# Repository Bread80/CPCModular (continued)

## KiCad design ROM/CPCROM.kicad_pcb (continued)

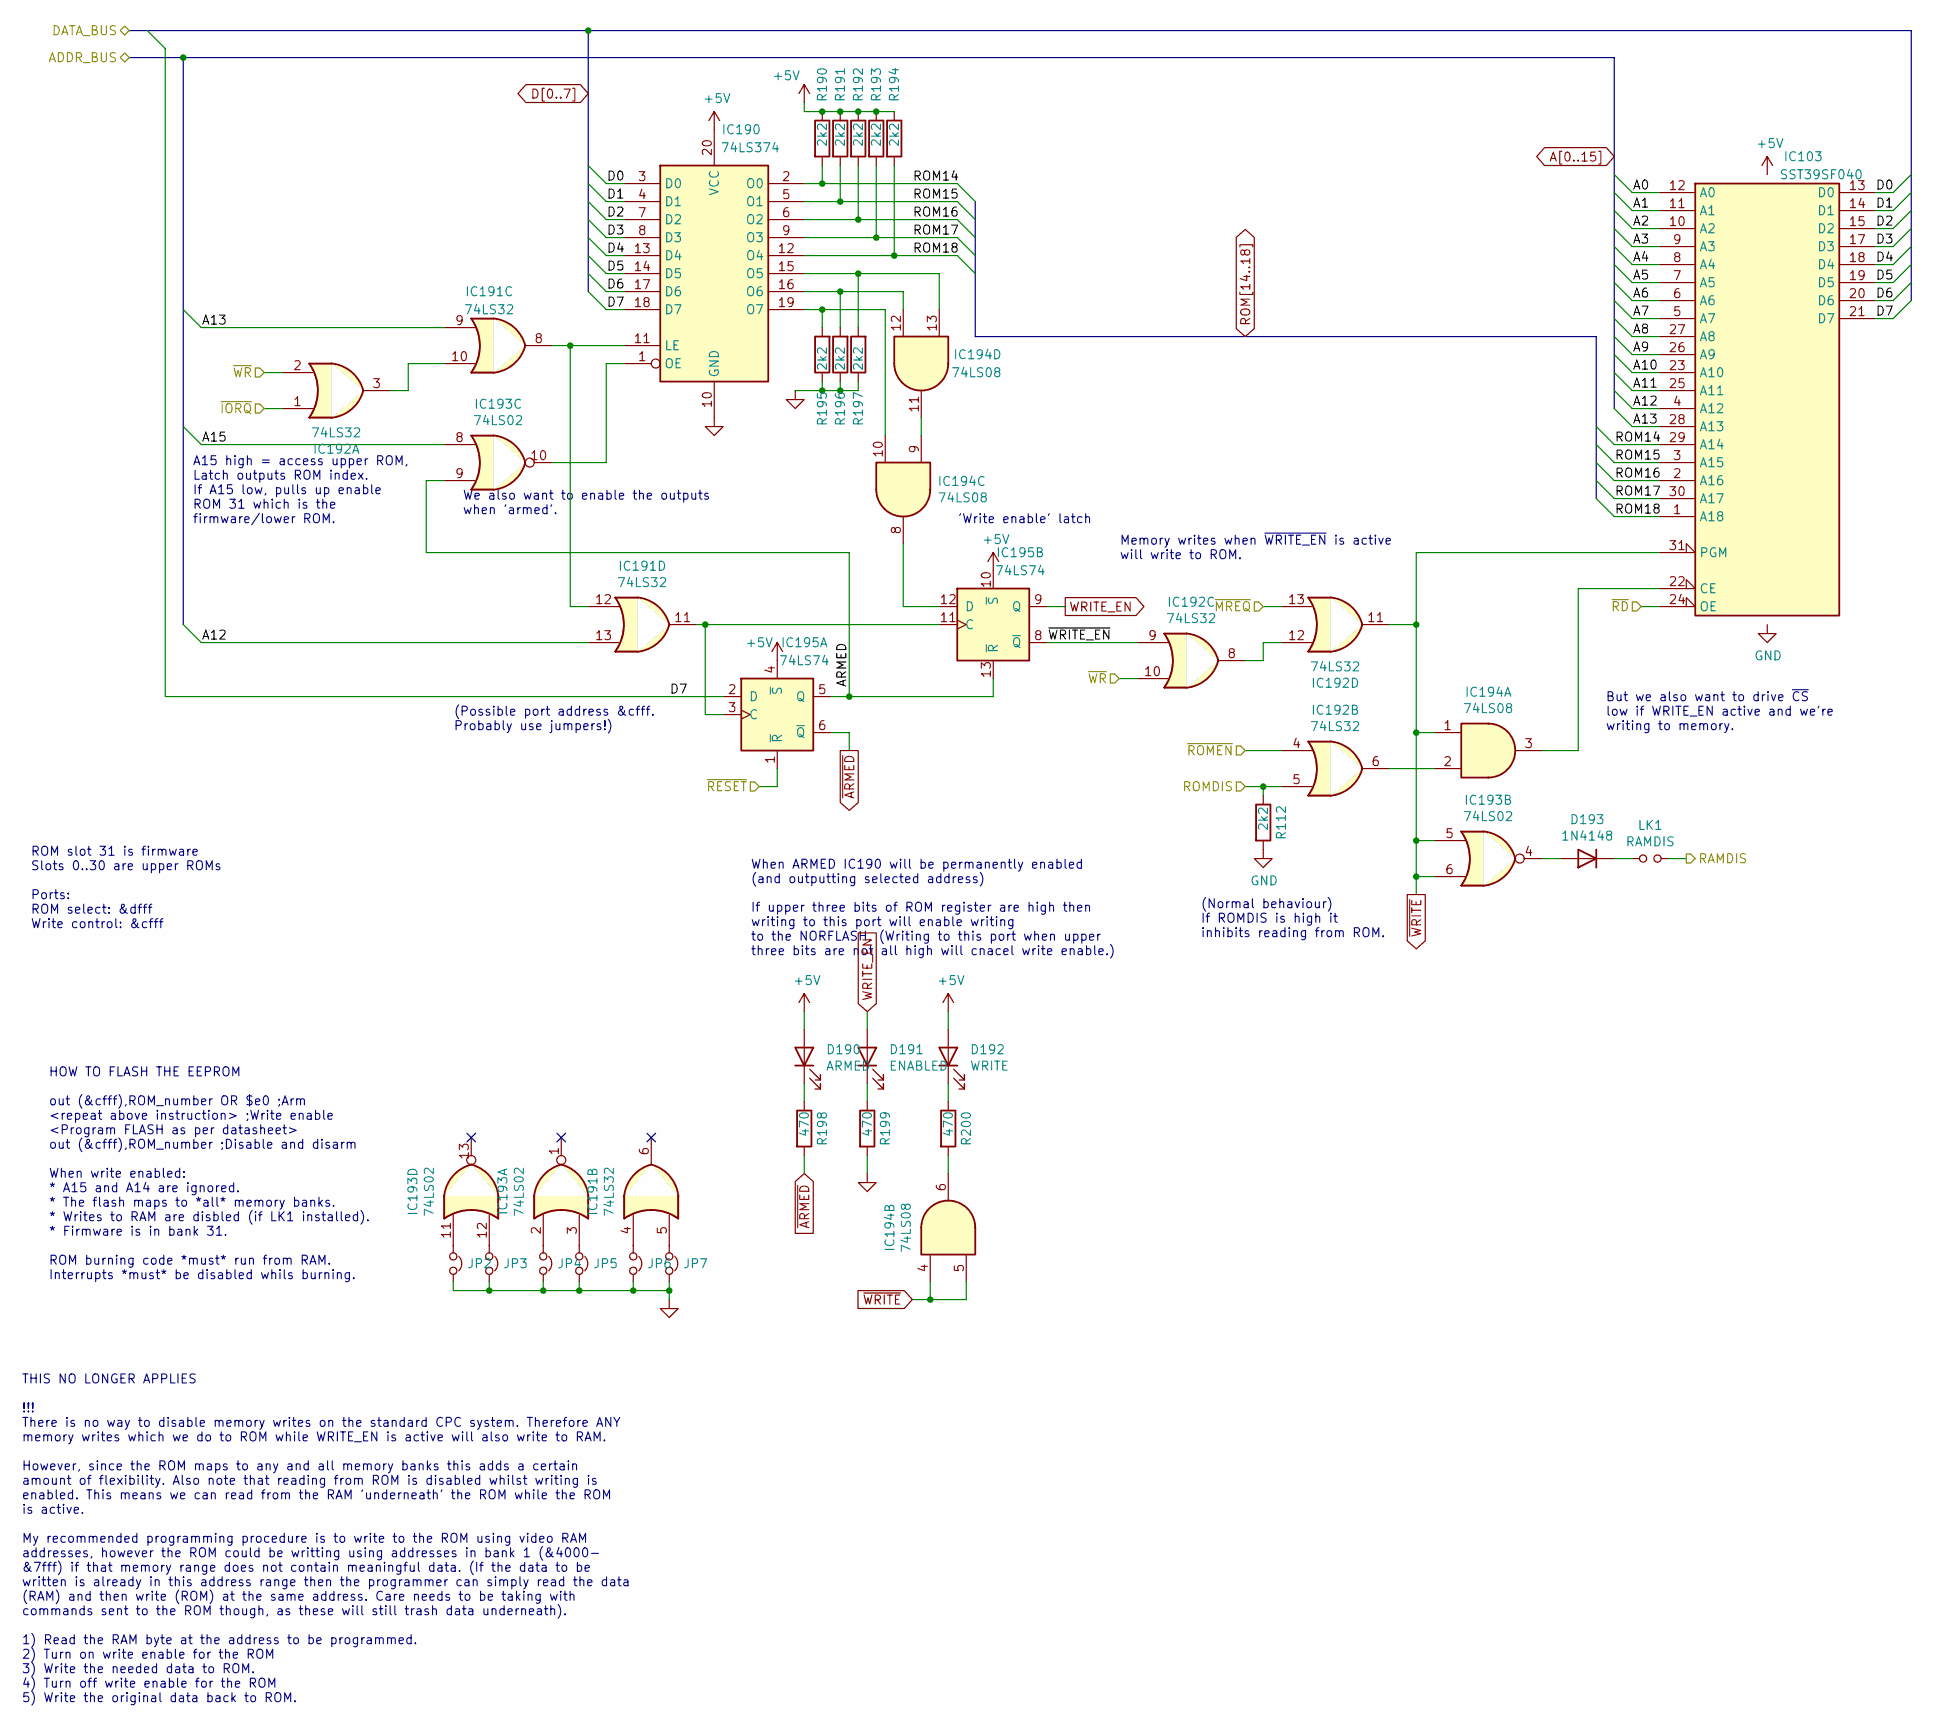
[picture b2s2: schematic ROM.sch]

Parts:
D190: ARMED; LED_D3.0mm
D191: ENABLED; LED_D3.0mm
D192: WRITE; LED_D3.0mm
D193: 1N4148; D_DO-35_SOD27_P7.62mm_Horizontal
IC103: SST39SF040; DIP_Socket-32_W11.9_W12.7_W15.24_W17.78_W18.5_3M_232-1285-0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
IC190: 74LS374; DIP-20_W7.62mm_Socket
IC191, IC192: 74LS32; DIP-14_W7.62mm_Socket
IC193: 74LS02; DIP-14_W7.62mm_Socket
IC194: 74LS08; DIP-14_W7.62mm_Socket
IC195: 74LS74; DIP-14_W7.62mm_Socket
JP2, JP3, JP4, JP5, JP6, JP7: Jumper_NC_Small; SolderJumper-2_P1.3mm_Bridged_RoundedPad1.0x1.5mm
LK1: RAMDIS; PinHeader_1x02_P2.54mm_Vertical
R112, R190, R191, R192, R193, R194, R195, R196, R197: 2k2; R_Axial_DIN0207_L6.3mm_D2.5mm_P7.62mm_Horizontal
R198, R199, R200: 470; R_Axial_DIN0207_L6.3mm_D2.5mm_P7.62mm_Horizontal

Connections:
/RAMDIS: LK1.2; also elsewhere on the board
/ROM/~WRITE_EN: IC192.9, IC195.8 (~Q)
/ROMDIS: IC192.5, R112.1; also elsewhere on the board
/~IORQ: IC192.1; also elsewhere on the board
/~MREQ: IC192.13; also elsewhere on the board
/~RD: IC103.24 (OE); also elsewhere on the board
/~RESET: IC195.1 (~R); also elsewhere on the board
/~ROMEN: IC192.4; also elsewhere on the board
A0: IC103.12 (A0); also elsewhere on the board
A1: IC103.11 (A1); also elsewhere on the board
A2: IC103.10 (A2); also elsewhere on the board
A3: IC103.9 (A3); also elsewhere on the board
A4: IC103.8 (A4); also elsewhere on the board
A5: IC103.7 (A5); also elsewhere on the board
A6: IC103.6 (A6); also elsewhere on the board
A7: IC103.5 (A7); also elsewhere on the board
A8: IC103.27 (A8); also elsewhere on the board
A9: IC103.26 (A9); also elsewhere on the board
A10: IC103.23 (A10); also elsewhere on the board
A11: IC103.25 (A11); also elsewhere on the board
A12: IC103.4 (A12), IC191.13; also elsewhere on the board
A13: IC103.28 (A13), IC191.9; also elsewhere on the board
D0: IC103.13 (D0), IC190.3 (D0); also elsewhere on the board
D1: IC103.14 (D1), IC190.4 (D1); also elsewhere on the board
D2: IC103.15 (D2), IC190.7 (D2); also elsewhere on the board
D3: IC103.17 (D3), IC190.8 (D3); also elsewhere on the board
D4: IC103.18 (D4), IC190.13 (D4); also elsewhere on the board
D5: IC103.19 (D5), IC190.14 (D5); also elsewhere on the board
D6: IC103.20 (D6), IC190.17 (D6); also elsewhere on the board
D7: IC103.21 (D7), IC190.18 (D7), IC195.2 (D); also elsewhere on the board
unnamed: D190.1 (K), R198.1
unnamed: D191.1 (K), R199.1
unnamed: D192.1 (K), R200.1
unnamed: D193.1 (K), LK1.1
unnamed: D193.2 (A), IC193.4
unnamed: IC103.22 (CE), IC194.3
unnamed: IC190.1 (OE), IC193.10
unnamed: IC190.11 (LE), IC191.8, IC191.12
unnamed: IC190.15 (O5), IC194.13, R197.2
unnamed: IC190.16 (O6), IC194.12, R196.2
unnamed: IC190.19 (O7), IC194.10, R195.2
unnamed: IC191.4, JP6.1
unnamed: IC191.5, JP7.1
unnamed: IC191.10, IC192.3
unnamed: IC192.6, IC194.2
unnamed: IC192.8, IC192.12
unnamed: IC193.2, JP4.1
unnamed: IC193.3, JP5.1
unnamed: IC194.6, R200.2
unnamed: IC194.9, IC194.11
ROM14: IC103.29 (A14), IC190.2 (O0), R190.2
ROM15: IC103.3 (A15), IC190.5 (O1), R191.2
ROM16: IC103.2 (A16), IC190.6 (O2), R192.2
ROM17: IC103.30 (A17), IC190.9 (O3), R193.2
ROM18: IC103.1 (A18), IC190.12 (O4), R194.2
WRITE_EN: D191.2 (A), IC195.9 (Q)
~ARMED: IC195.6 (~Q), R198.2

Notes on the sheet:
A15 high = access upper ROM, Latch outputs ROM index. If A15 low, pulls up enable ROM 31 which is the firmware/lower ROM.
'Write enable' latch
(Possible port address &cfff. Probably use jumpers!)
If upper three bits of ROM register are high then writing to this port will enable writing to the NORFLASH. (Writing to this port when upper three bits are not all high will cnacel write enable.)
Memory writes when ~WRITE_EN~ is active will write to ROM.
(Normal behaviour) If ROMDIS is high it inhibits reading from ROM.
But we also want to drive ~CS~ low if WRITE_EN active and we're writing to memory.
THIS NO LONGER APPLIES !!! There is no way to disable memory writes on the standard CPC system. Therefore ANY memory writes which we do to ROM while WRITE_EN is active will also write to RAM. However, since the ROM maps to any and all memory banks this adds a certain amount of flexibility. Also not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
HOW TO FLASH THE EEPROM out (&cfff),ROM_number OR $e0 ;Arm <repeat above instruction> ;Write enable <Program FLASH as per datasheet> out (&cfff),ROM_number ;Disable and disarm When write enabled: * A15 and A14 are ignored. * The flash maps to *all* memory banks. * Writes to RAM are disbled (if LK1 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
We also want to enable the outputs when 'armed'.
When ARMED IC190 will be permanently enabled (and outputting selected address)
ROM slot 31 is firmware Slots 0..30 are upper ROMs Ports: ROM select: &dfff Write control: &cfff

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
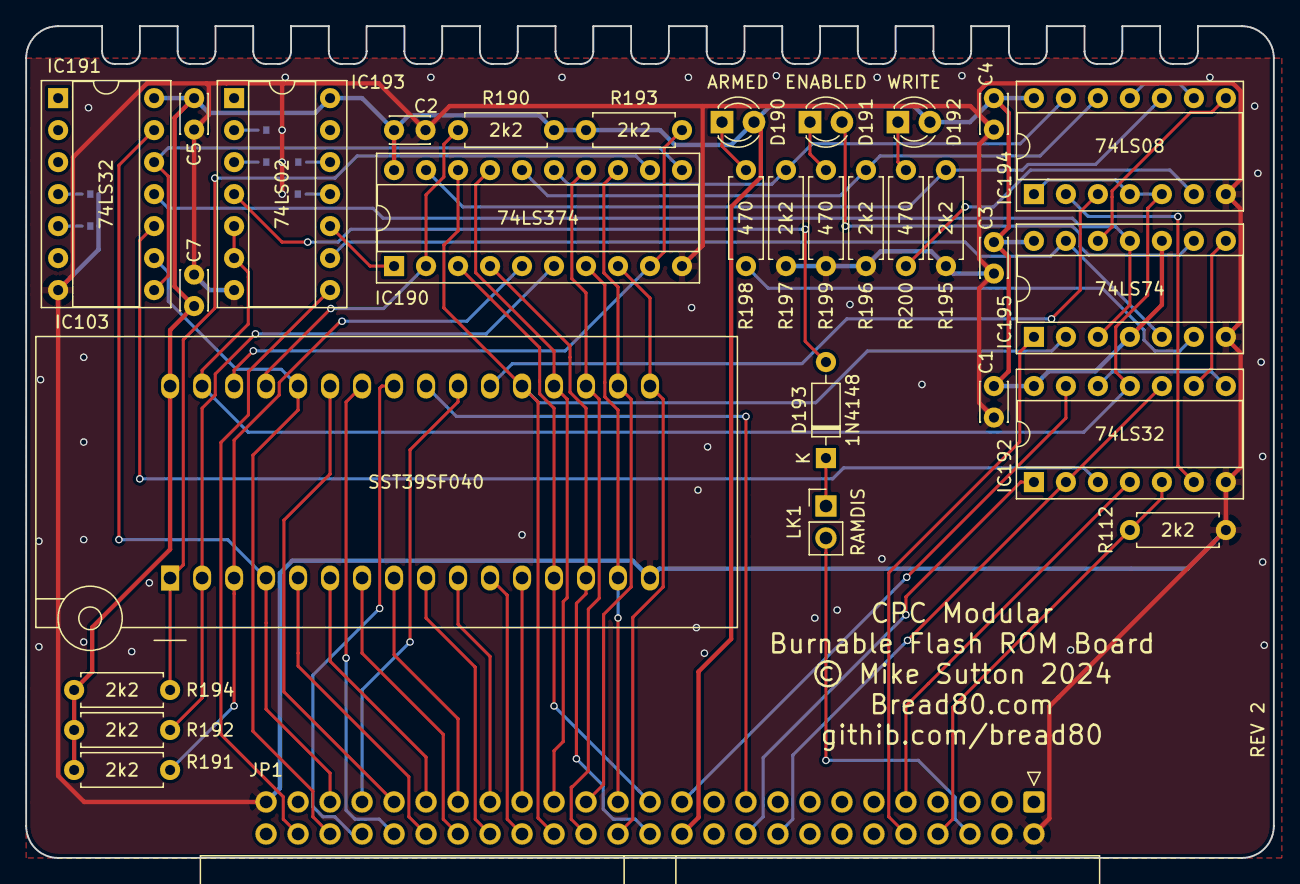
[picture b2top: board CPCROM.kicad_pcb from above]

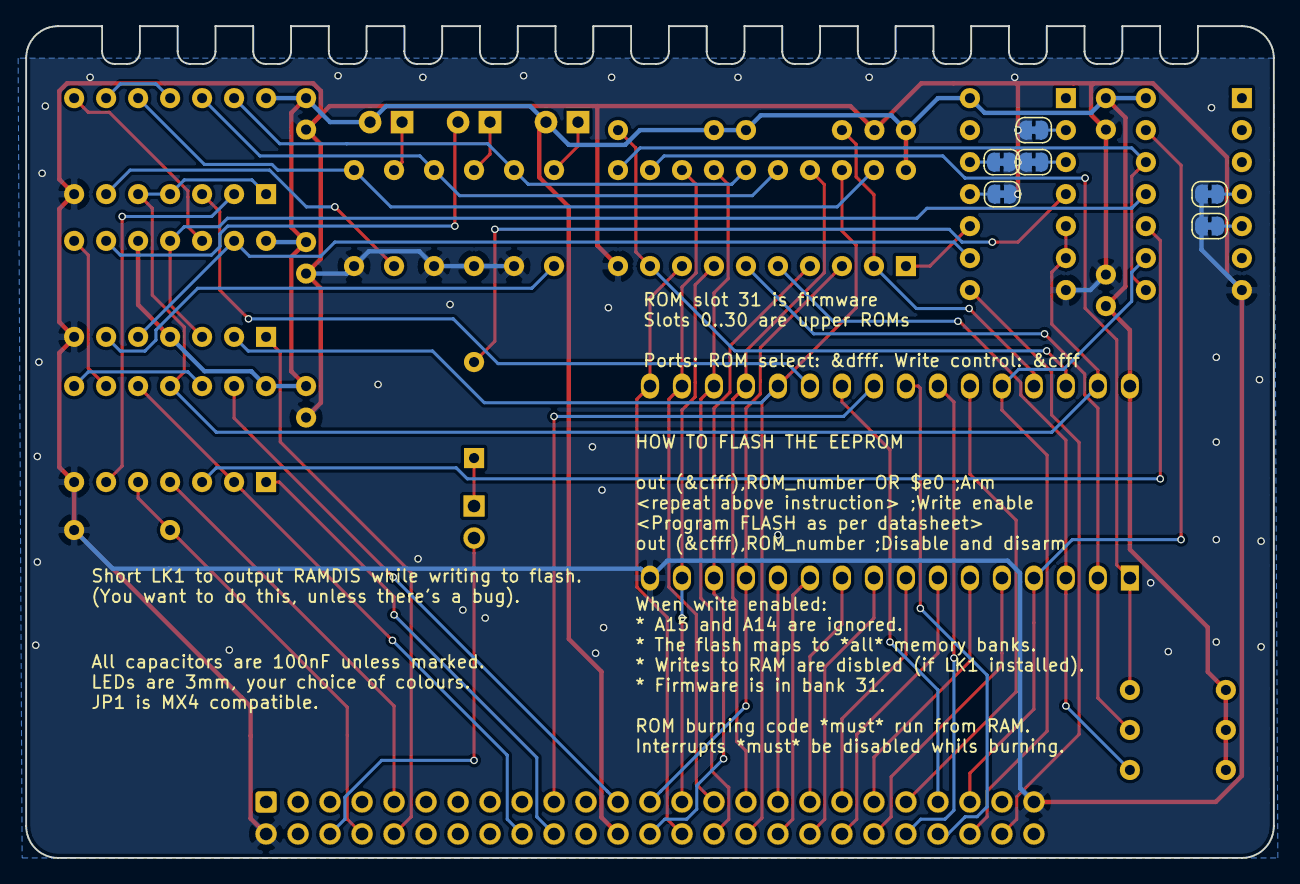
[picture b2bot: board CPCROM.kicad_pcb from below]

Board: 2 copper layers, 99.1 x 66.0 mm, 37 parts (6 on the bottom side), 67 nets.

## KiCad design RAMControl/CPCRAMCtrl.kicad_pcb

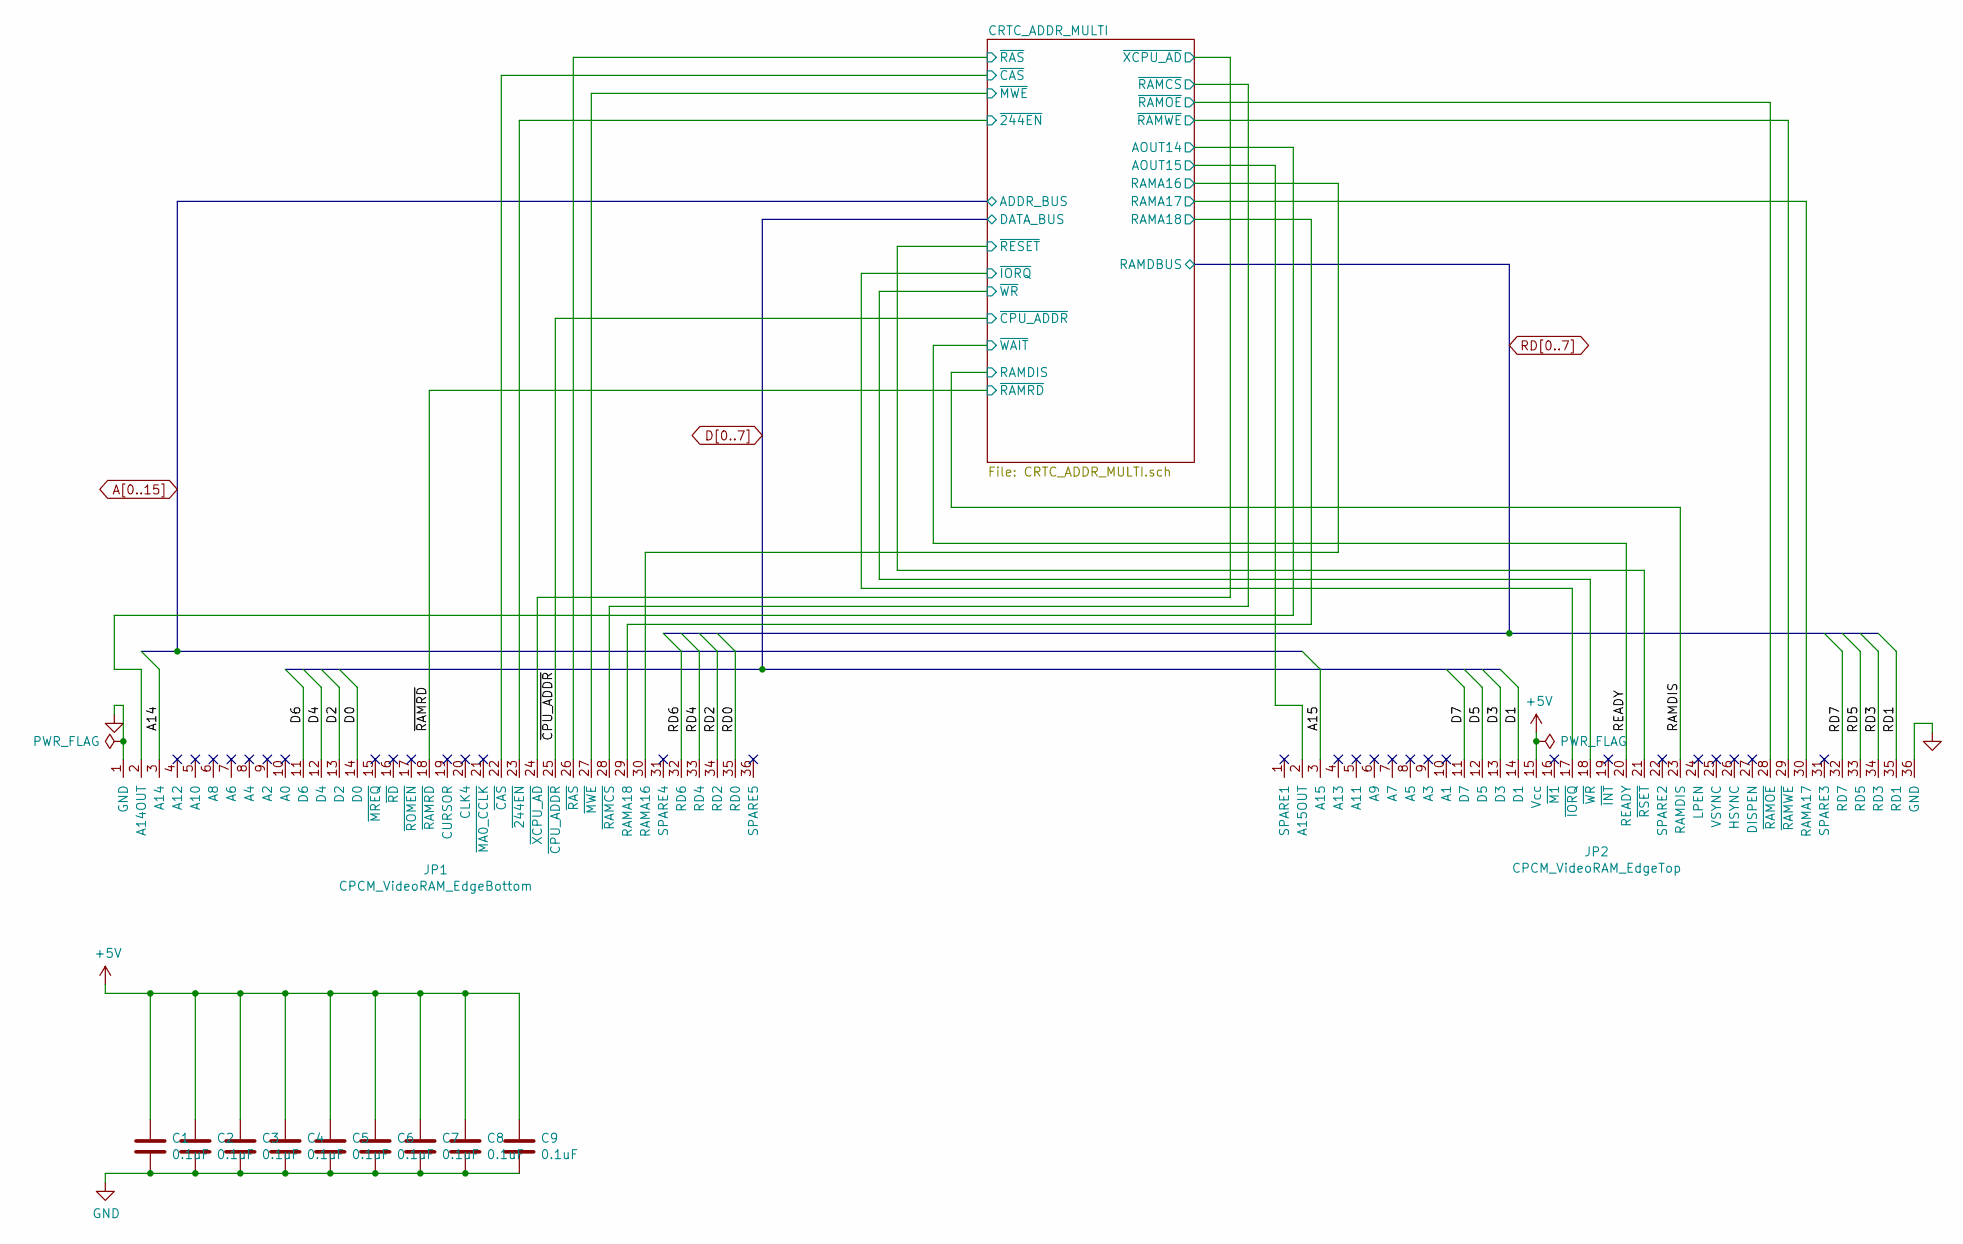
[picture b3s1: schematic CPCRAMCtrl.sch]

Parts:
C1, C2, C3, C4, C5, C6, C7, C8, C9: 0.1uF; C_Disc_D3.0mm_W2.0mm_P2.50mm
JP1: CPCM_VideoRAM_EdgeBottom; Edge36_2.54PS
JP2: CPCM_VideoRAM_EdgeTop; Edge36_2.54PS

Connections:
+5V: C1.1, C2.1, C3.1, C4.1, C5.1, C6.1, C7.1, C8.1, C9.1, JP2.15 (Vcc); also elsewhere on the board
/CRTC_ADDR_MULTI/AOUT14: JP1.2 (A14OUT); also elsewhere on the board
/CRTC_ADDR_MULTI/AOUT15: JP2.2 (A15OUT); also elsewhere on the board
/CRTC_ADDR_MULTI/RAMA16: JP1.30 (RAMA16); also elsewhere on the board
/CRTC_ADDR_MULTI/RAMA17: JP2.30 (RAMA17); also elsewhere on the board
/CRTC_ADDR_MULTI/RAMA18: JP1.29 (RAMA18); also elsewhere on the board
/CRTC_ADDR_MULTI/~244EN: JP1.23 (~244EN); also elsewhere on the board
/CRTC_ADDR_MULTI/~CAS: JP1.22 (~CAS); also elsewhere on the board
/CRTC_ADDR_MULTI/~IORQ: JP2.17 (~IORQ); also elsewhere on the board
/CRTC_ADDR_MULTI/~MWE: JP1.27 (~MWE); also elsewhere on the board
/CRTC_ADDR_MULTI/~RAMCS: JP1.28 (~RAMCS); also elsewhere on the board
/CRTC_ADDR_MULTI/~RAMOE: JP2.28 (~RAMOE); also elsewhere on the board
/CRTC_ADDR_MULTI/~RAMWE: JP2.29 (~RAMWE); also elsewhere on the board
/CRTC_ADDR_MULTI/~RAS: JP1.26 (~RAS); also elsewhere on the board
/CRTC_ADDR_MULTI/~RESET: JP2.21 (~RSET); also elsewhere on the board
/CRTC_ADDR_MULTI/~WR: JP2.18 (~WR); also elsewhere on the board
/CRTC_ADDR_MULTI/~XCPU_AD: JP1.24 (~XCPU_AD); also elsewhere on the board
/RAMDIS: JP2.23 (RAMDIS); also elsewhere on the board
/READY: JP2.20 (READY); also elsewhere on the board
/~CPU_ADDR: JP1.25 (~CPU_ADDR); also elsewhere on the board
/~RAMRD: JP1.18 (~RAMRD); also elsewhere on the board
A14: JP1.3 (A14); also elsewhere on the board
A15: JP2.3 (A15); also elsewhere on the board
D0: JP1.14 (D0); also elsewhere on the board
D1: JP2.14 (D1); also elsewhere on the board
D2: JP1.13 (D2); also elsewhere on the board
D3: JP2.13 (D3); also elsewhere on the board
D4: JP1.12 (D4); also elsewhere on the board
D5: JP2.12 (D5); also elsewhere on the board
D6: JP1.11 (D6); also elsewhere on the board
D7: JP2.11 (D7); also elsewhere on the board
GND: C1.2, C2.2, C3.2, C4.2, C5.2, C6.2, C7.2, C8.2, C9.2, JP1.1 (GND), JP2.36 (GND); also elsewhere on the board
RD0: JP1.35 (RD0); also elsewhere on the board
RD1: JP2.35 (RD1); also elsewhere on the board
RD2: JP1.34 (RD2); also elsewhere on the board
RD3: JP2.34 (RD3); also elsewhere on the board
RD4: JP1.33 (RD4); also elsewhere on the board
RD5: JP2.33 (RD5); also elsewhere on the board
RD6: JP1.32 (RD6); also elsewhere on the board
RD7: JP2.32 (RD7); also elsewhere on the board

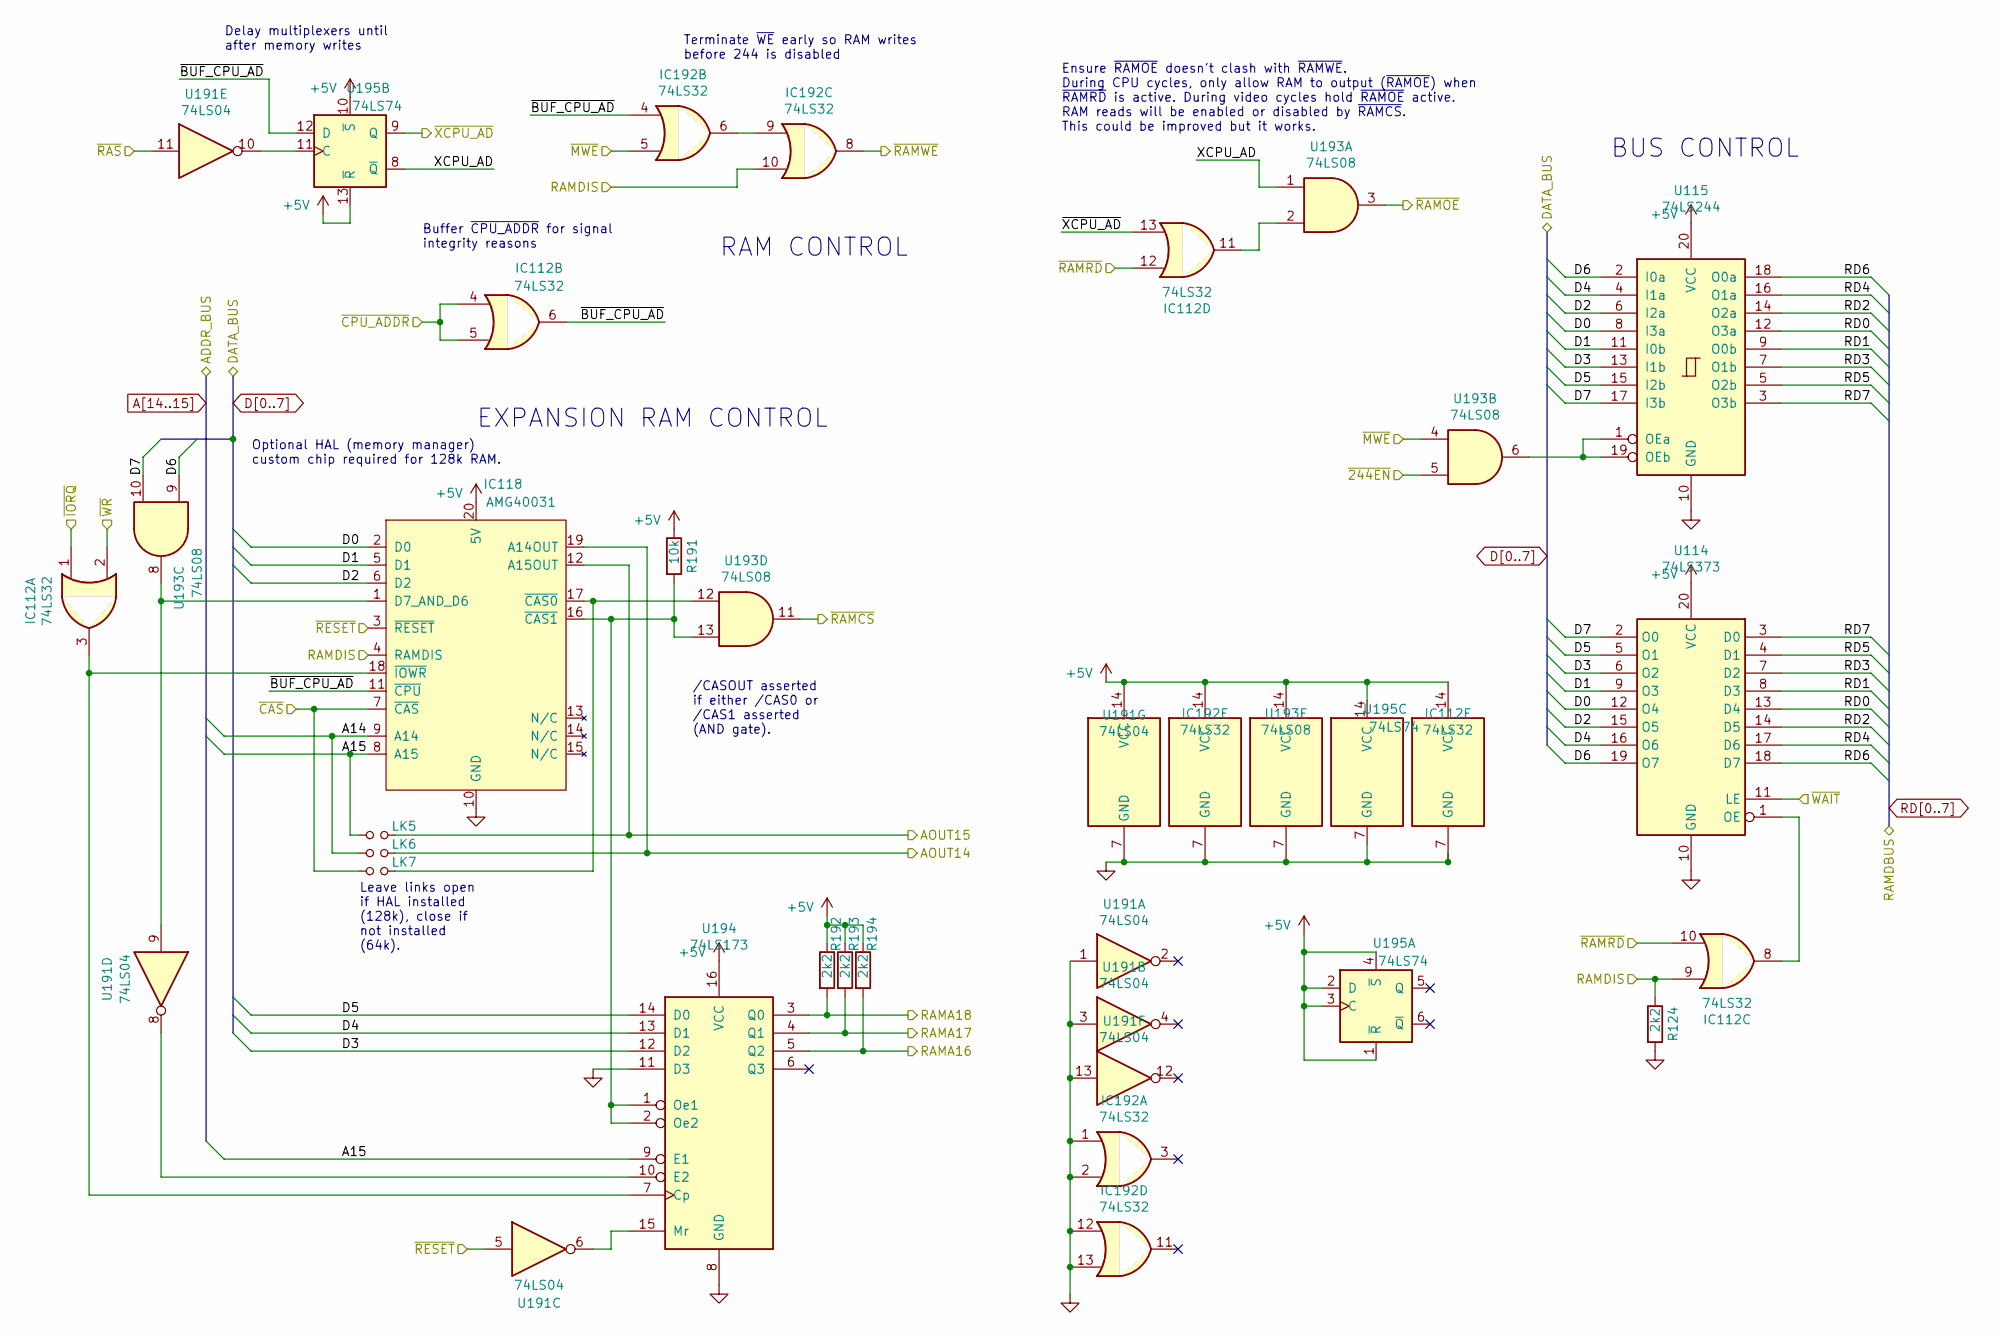
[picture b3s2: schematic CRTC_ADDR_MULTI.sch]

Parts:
IC112, IC192: 74LS32; DIP-14_W7.62mm_Socket
IC118: AMG40031; DIP-20_W7.62mm
LK5, LK6, LK7: Jumper_NO_Small; PinHeader_1x02_P2.54mm_Vertical
R124, R192, R193, R194: 2k2; R_Axial_DIN0207_L6.3mm_D2.5mm_P7.62mm_Horizontal
R191: 10k; R_Axial_DIN0207_L6.3mm_D2.5mm_P7.62mm_Horizontal
U114: 74LS373; DIP-20_W7.62mm_Socket
U115: 74LS244; DIP-20_W7.62mm_Socket
U191: 74LS04; DIP-14_W7.62mm_Socket
U193: 74LS08; DIP-14_W7.62mm_Socket
U194: 74LS173; DIP-16_W7.62mm_Socket
U195: 74LS74; DIP-14_W7.62mm_Socket

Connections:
+5V: IC112.14 (VCC), IC118.20 (5V), IC192.14 (VCC), R191.1, R192.1, R193.1, R194.1, U114.20 (VCC), U115.20 (VCC), U191.14 (VCC), U193.14 (VCC), U194.16 (VCC), U195.1 (~R), U195.2 (D), U195.3 (C), U195.4 (~S), U195.10 (~S), U195.13 (~R), U195.14 (VCC); also elsewhere on the board
/CRTC_ADDR_MULTI/AOUT14: IC118.19 (A14OUT), LK6.2; also elsewhere on the board
/CRTC_ADDR_MULTI/AOUT15: IC118.12 (A15OUT), LK5.2; also elsewhere on the board
/CRTC_ADDR_MULTI/RAMA16: R194.2, U194.5 (Q2); also elsewhere on the board
/CRTC_ADDR_MULTI/RAMA17: R193.2, U194.4 (Q1); also elsewhere on the board
/CRTC_ADDR_MULTI/RAMA18: R192.2, U194.3 (Q0); also elsewhere on the board
/CRTC_ADDR_MULTI/XCPU_AD: U193.1, U195.8 (~Q)
/CRTC_ADDR_MULTI/~244EN: U193.5; also elsewhere on the board
/CRTC_ADDR_MULTI/~BUF_CPU_AD: IC112.6, IC118.11 (~CPU), IC192.4, U195.12 (D)
/CRTC_ADDR_MULTI/~CAS: IC118.7 (~CAS), LK7.1; also elsewhere on the board
/CRTC_ADDR_MULTI/~IORQ: IC112.1; also elsewhere on the board
/CRTC_ADDR_MULTI/~MWE: IC192.5, U193.4; also elsewhere on the board
/CRTC_ADDR_MULTI/~RAMCS: U193.11; also elsewhere on the board
/CRTC_ADDR_MULTI/~RAMOE: U193.3; also elsewhere on the board
/CRTC_ADDR_MULTI/~RAMWE: IC192.8; also elsewhere on the board
/CRTC_ADDR_MULTI/~RAS: U191.11; also elsewhere on the board
/CRTC_ADDR_MULTI/~RESET: IC118.3 (~RESET), U191.5; also elsewhere on the board
/CRTC_ADDR_MULTI/~WR: IC112.2; also elsewhere on the board
/CRTC_ADDR_MULTI/~XCPU_AD: IC112.13, U195.9 (Q); also elsewhere on the board
/RAMDIS: IC112.9, IC118.4 (RAMDIS), IC192.10, R124.1; also elsewhere on the board
/READY: U114.11 (LE); also elsewhere on the board
/~CPU_ADDR: IC112.4, IC112.5; also elsewhere on the board
/~RAMRD: IC112.10, IC112.12; also elsewhere on the board
A14: IC118.9 (A14), LK6.1; also elsewhere on the board
A15: IC118.8 (A15), LK5.1, U194.9 (E1); also elsewhere on the board
D0: IC118.2 (D0), U114.12 (O4), U115.8 (I3a); also elsewhere on the board
D1: IC118.5 (D1), U114.9 (O3), U115.11 (I0b); also elsewhere on the board
D2: IC118.6 (D2), U114.15 (O5), U115.6 (I2a); also elsewhere on the board
D3: U114.6 (O2), U115.13 (I1b), U194.12 (D2); also elsewhere on the board
D4: U114.16 (O6), U115.4 (I1a), U194.13 (D1); also elsewhere on the board
D5: U114.5 (O1), U115.15 (I2b), U194.14 (D0); also elsewhere on the board
D6: U114.19 (O7), U115.2 (I0a), U193.9; also elsewhere on the board
D7: U114.2 (O0), U115.17 (I3b), U193.10; also elsewhere on the board
GND: IC112.7 (GND), IC118.10 (GND), IC192.1, IC192.2, IC192.7 (GND), IC192.12, IC192.13, R124.2, U114.10 (GND), U115.10 (GND), U191.1, U191.3, U191.7 (GND), U191.13, U193.7 (GND), U194.8 (GND), U194.11 (D3), U195.7 (GND); also elsewhere on the board
unnamed: IC112.3, IC118.18 (~IOWR), U194.7 (Cp)
unnamed: IC112.8, U114.1 (OE)
unnamed: IC112.11, U193.2
unnamed: IC118.1 (D7_AND_D6), U191.9, U193.8
unnamed: IC118.16 (~CAS1), R191.2, U193.13, U194.1 (Oe1), U194.2 (Oe2)
unnamed: IC118.17 (~CAS0), LK7.2, U193.12
unnamed: IC192.6, IC192.9
unnamed: U115.1 (OEa), U115.19 (OEb), U193.6
unnamed: U191.6, U194.15 (Mr)
unnamed: U191.8, U194.10 (E2)
unnamed: U191.10, U195.11 (C)
RD0: U114.13 (D4), U115.12 (O3a); also elsewhere on the board
RD1: U114.8 (D3), U115.9 (O0b); also elsewhere on the board
RD2: U114.14 (D5), U115.14 (O2a); also elsewhere on the board
RD3: U114.7 (D2), U115.7 (O1b); also elsewhere on the board
RD4: U114.17 (D6), U115.16 (O1a); also elsewhere on the board
RD5: U114.4 (D1), U115.5 (O2b); also elsewhere on the board
RD6: U114.18 (D7), U115.18 (O0a); also elsewhere on the board
RD7: U114.3 (D0), U115.3 (O3b); also elsewhere on the board

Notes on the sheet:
Leave links open if HAL installed (128k), close if not installed (64k).
Optional HAL (memory manager) custom chip required for 128k RAM.
/CASOUT asserted if either /CAS0 or /CAS1 asserted (AND gate).
BUS CONTROL
RAM CONTROL
EXPANSION RAM CONTROL
Buffer ~CPU_ADDR~ for signal integrity reasons
Delay multiplexers until after memory writes
Terminate ~WE~ early so RAM writes before 244 is disabled
Ensure ~RAMOE~ doesn't clash with ~RAMWE~. During CPU cycles, only allow RAM to output (~RAMOE~) when ~RAMRD~ is active. During video cycles hold ~RAMOE~ active. RAM reads will be enabled or disabled by ~RAMCS~. This could be improved but it works.

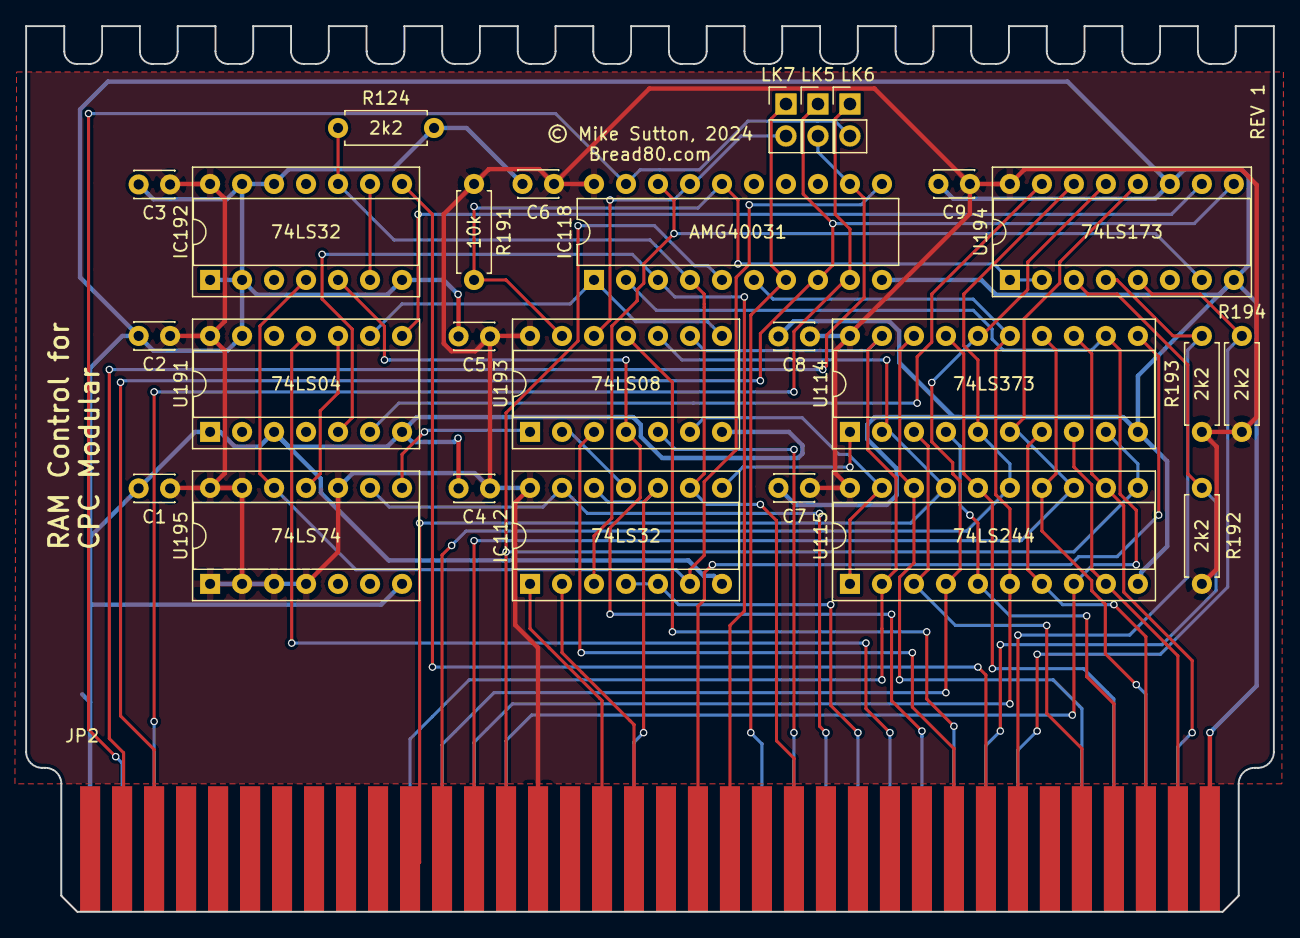
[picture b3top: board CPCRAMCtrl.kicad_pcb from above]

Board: 2 copper layers, 99.1 x 70.3 mm, 28 parts (1 on the bottom side), 53 nets.

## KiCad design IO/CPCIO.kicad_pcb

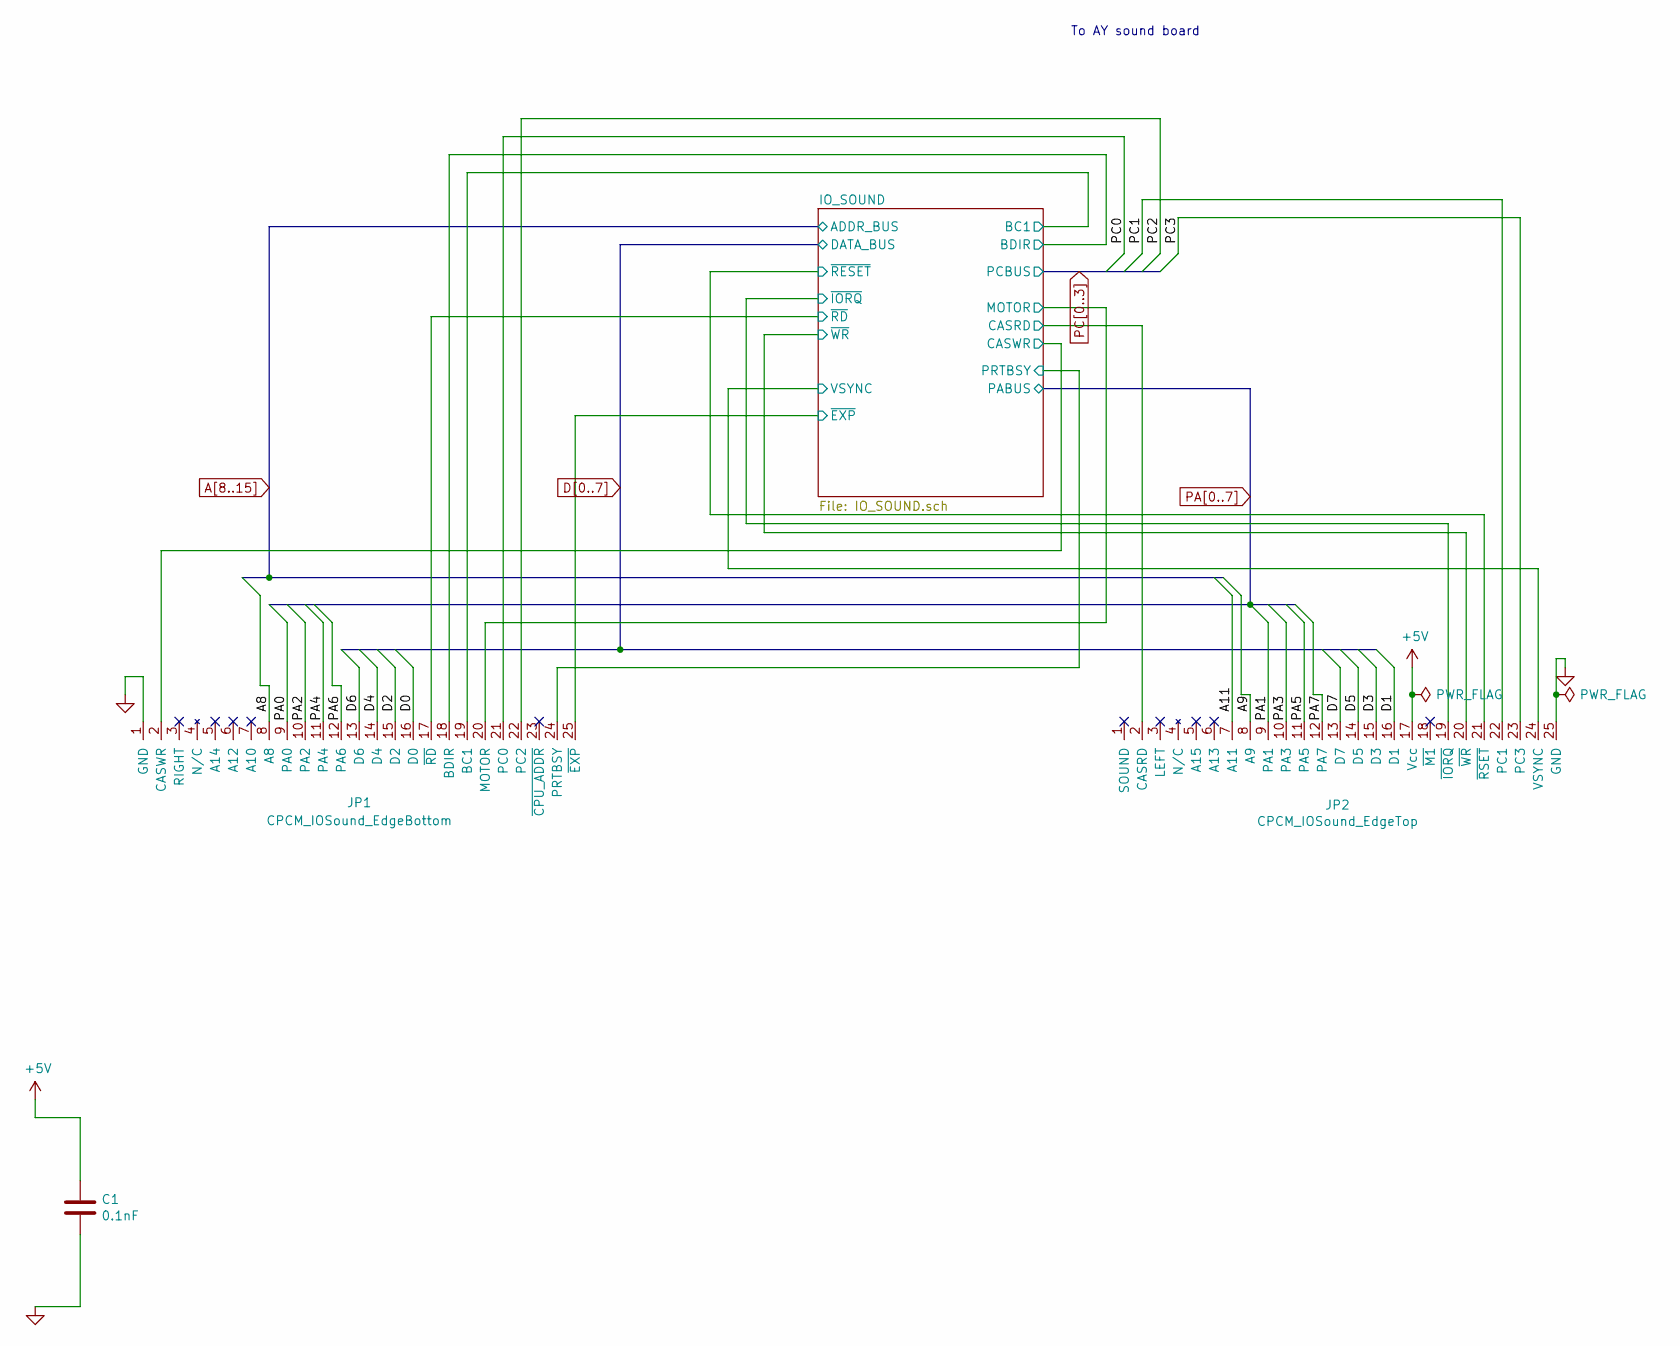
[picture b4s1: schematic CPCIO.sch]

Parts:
C1: 0.1nF; C_Disc_D3.0mm_W2.0mm_P2.50mm
JP1: CPCM_IOSound_EdgeBottom; Edge25_2.54PS
JP2: CPCM_IOSound_EdgeTop; Edge25_2.54PS

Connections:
+5V: C1.1, JP2.17 (Vcc); also elsewhere on the board
/IO_SOUND/BC1: JP1.19 (BC1); also elsewhere on the board
/IO_SOUND/BDIR: JP1.18 (BDIR); also elsewhere on the board
/IO_SOUND/CASRD: JP2.2 (CASRD); also elsewhere on the board
/IO_SOUND/CASWR: JP1.2 (CASWR); also elsewhere on the board
/IO_SOUND/MOTOR: JP1.20 (MOTOR); also elsewhere on the board
/IO_SOUND/PRTBSY: JP1.24 (PRTBSY); also elsewhere on the board
/IO_SOUND/VSYNC: JP2.24 (VSYNC); also elsewhere on the board
/IO_SOUND/~EXP: JP1.25 (~EXP); also elsewhere on the board
/IO_SOUND/~IORQ: JP2.19 (~IORQ); also elsewhere on the board
/IO_SOUND/~RD: JP1.17 (~RD); also elsewhere on the board
/IO_SOUND/~RESET: JP2.21 (~RSET); also elsewhere on the board
/IO_SOUND/~WR: JP2.20 (~WR); also elsewhere on the board
A8: JP1.8 (A8); also elsewhere on the board
A9: JP2.8 (A9); also elsewhere on the board
A11: JP2.7 (A11); also elsewhere on the board
D0: JP1.16 (D0); also elsewhere on the board
D1: JP2.16 (D1); also elsewhere on the board
D2: JP1.15 (D2); also elsewhere on the board
D3: JP2.15 (D3); also elsewhere on the board
D4: JP1.14 (D4); also elsewhere on the board
D5: JP2.14 (D5); also elsewhere on the board
D6: JP1.13 (D6); also elsewhere on the board
D7: JP2.13 (D7); also elsewhere on the board
GND: C1.2, JP1.1 (GND), JP2.25 (GND); also elsewhere on the board
PA0: JP1.9 (PA0); also elsewhere on the board
PA1: JP2.9 (PA1); also elsewhere on the board
PA2: JP1.10 (PA2); also elsewhere on the board
PA3: JP2.10 (PA3); also elsewhere on the board
PA4: JP1.11 (PA4); also elsewhere on the board
PA5: JP2.11 (PA5); also elsewhere on the board
PA6: JP1.12 (PA6); also elsewhere on the board
PA7: JP2.12 (PA7); also elsewhere on the board
PC0: JP1.21 (PC0); also elsewhere on the board
PC1: JP2.22 (PC1); also elsewhere on the board
PC2: JP1.22 (PC2); also elsewhere on the board
PC3: JP2.23 (PC3); also elsewhere on the board

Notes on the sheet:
To AY sound board
